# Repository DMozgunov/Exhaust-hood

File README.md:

# Exhaust-hood
Fan controller for a DIY exhaust hood. PIC16F628 + MPASM

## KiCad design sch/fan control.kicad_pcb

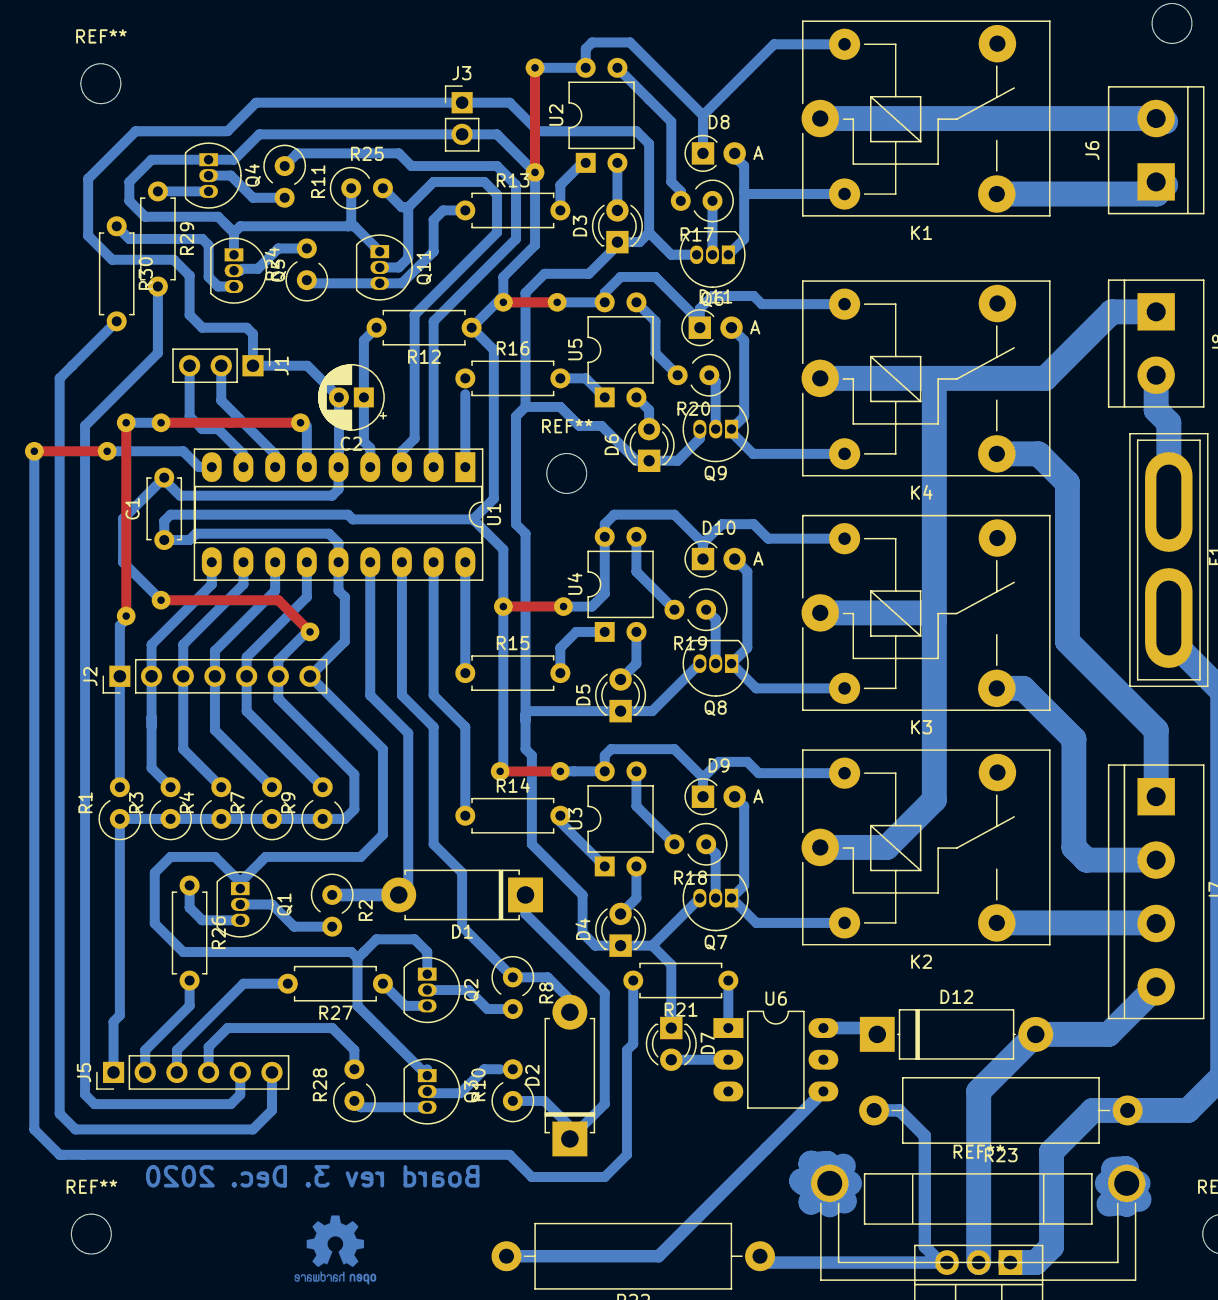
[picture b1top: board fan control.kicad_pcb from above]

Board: 2 copper layers, 71 parts (0 on the bottom side), 69 nets.

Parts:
C1: 100nF; C_Disc_D4.7mm_W2.5mm_P5.00mm
C2: 1mkF; CP_Radial_D5.0mm_P2.00mm
D1, D2: 1N4148; D_5W_P10.16mm_Horizontal
D3, D4, D5, D6, D7: LED; LED_D3.0mm
D8, D9, D10, D11: 1N4148; D_A-405_P2.54mm_Vertical_AnodeUp
D12: FR207; D_5W_P12.70mm_Horizontal
F1: Fuse; Fuse_Blade_ATO_directSolder
J1: Serial Port; PinHeader_1x03_P2.54mm_Vertical
J2: Buttons; PinHeader_1x07_P2.54mm_Vertical
J3: Power 5V; PinHeader_1x02_P2.54mm_Vertical
J5: STATUS LEDs; PinHeader_1x06_P2.54mm_Vertical
J6: Light; TerminalBlock_bornier-2_P5.08mm
J7: Motor cois; TerminalBlock_bornier-4_P5.08mm
J8: AC 220v in; TerminalBlock_bornier-2_P5.08mm
K1, K2, K3, K4: SANYOU_SRD_Form_C; Relay_SPDT_SANYOU_SRD_Series_Form_C
Q1, Q2, Q3, Q4, Q5, Q6, Q7, Q8, Q9, Q11: BC547; TO-92_Inline
Q10: BT136-800; TO-220-3_Vertical
R1, R3, R4, R7, R9: 10k; R_Axial_DIN0309_L9.0mm_D3.2mm_P2.54mm_Vertical
R2, R8, R10, R11, R17, R18, R19, R20, R24, R25: 1k; R_Axial_DIN0309_L9.0mm_D3.2mm_P2.54mm_Vertical
R12: 10k; R_Axial_DIN0207_L6.3mm_D2.5mm_P7.62mm_Horizontal
R13, R14, R15, R16: 1k; R_Axial_DIN0207_L6.3mm_D2.5mm_P7.62mm_Horizontal
R21, R26, R27, R29, R30: 240; R_Axial_DIN0207_L6.3mm_D2.5mm_P7.62mm_Horizontal
R22, R23: 330; R_Axial_DIN0516_L15.5mm_D5.0mm_P20.32mm_Horizontal
R28: 240; R_Axial_DIN0309_L9.0mm_D3.2mm_P2.54mm_Vertical
U1: PIC16F628-xxIP; DIP-18_W7.62mm_Socket_LongPads
U2, U3, U4, U5: PC817; DIP-4_W7.62mm
U6: MOC3041M; DIP-6_W7.62mm_LongPads

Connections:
+5V: C1.1, D8.1, D9.1, D10.1, D11.1, J2.7, J3.2, K1.5, K2.5, K3.5, K4.5, Q1.1, Q2.1, Q3.1, Q4.1, Q5.1, Q11.1, R12.1, R25.1, U1.14, U2.4, U3.4, U4.4, U5.4
unnamed: C2.1, R12.2, U1.4
unnamed: D1.1, D2.1, R10.1
unnamed: D1.2, R2.1, U1.15
unnamed: D2.2, R8.1, U1.16
unnamed: D3.2, U2.2
unnamed: D4.2, U3.2
unnamed: D5.2, U4.2
unnamed: D6.2, U5.2
unnamed: D7.2, U6.2
unnamed: D8.2, K1.2, Q6.1
unnamed: D9.2, K2.2, Q7.1
unnamed: D10.2, K3.2, Q8.1
unnamed: D11.2, K4.2, Q9.1
unnamed: D12.1, U6.6
unnamed: D12.2, J7.4, Q10.2
unnamed: F1.1, J8.2
unnamed: F1.2, Q10.1, R23.1
unnamed: J1.2, U1.7
unnamed: J1.3, U1.8
unnamed: J2.1, R1.2, U1.6
unnamed: J2.2, R3.2, U1.10
unnamed: J2.3, R4.2, U1.11
unnamed: J2.4, R7.2, U1.12
unnamed: J2.5, R9.2, U1.13
unnamed: J5.2, R26.2
unnamed: J5.3, R27.2
unnamed: J5.4, R28.2
unnamed: J5.5, R29.2
unnamed: J5.6, R30.2
unnamed: J6.1, K1.3
unnamed: J6.2, K1.1
unnamed: J7.1, K4.3
unnamed: J7.2, K3.3
unnamed: J7.3, K2.3
unnamed: J8.1, K2.1, K3.1, K4.1
unnamed: Q1.2, R2.2
unnamed: Q1.3, R26.1
unnamed: Q2.2, R8.2
unnamed: Q2.3, R27.1
unnamed: Q3.2, R10.2
unnamed: Q3.3, R28.1
unnamed: Q4.2, R11.2
unnamed: Q4.3, R29.1
unnamed: Q5.2, R24.2
unnamed: Q5.3, R30.1
unnamed: Q6.2, R17.1
unnamed: Q7.2, R18.1
unnamed: Q8.2, R19.1
unnamed: Q9.2, R20.1
unnamed: Q10.3, R22.1, R23.2
unnamed: Q11.2, R25.2, U1.3
unnamed: Q11.3, R13.1, R24.1
unnamed: R11.1, U1.2
unnamed: R13.2, U2.1
unnamed: R14.1, U1.17
unnamed: R14.2, U3.1
unnamed: R15.1, U1.18
unnamed: R15.2, U4.1
unnamed: R16.1, U1.1
unnamed: R16.2, U5.1
unnamed: R17.2, U2.3
unnamed: R18.2, U3.3
unnamed: R19.2, U4.3
unnamed: R20.2, U5.3
unnamed: R21.1, U6.1
unnamed: R21.2, U1.9
unnamed: R22.2, U6.4
VSS: C1.2, C2.2, D3.1, D4.1, D5.1, D6.1, D7.1, J1.1, J2.6, J3.1, J5.1, Q6.3, Q7.3, Q8.3, Q9.3, R1.1, R3.1, R4.1, R7.1, R9.1, U1.5

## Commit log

2018-08-05 Added KiCad SCH
2018-08-05 commented a bit
2018-08-08 Schematics has changed completely
2018-08-08 housekeeping
2018-08-08 what is going on with my sch? merge killed my work
2020-12-08 new rev 3
2020-12-08 Changed compiler
2020-12-09 Changed pcb
2020-12-13 PCB changed - new heatsynk
2020-12-14 pcb - plot
